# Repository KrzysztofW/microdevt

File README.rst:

Upstream Author: Krzysztof Witek

Copyright:
	 Copyright (c) 2017 Krzysztof Witek

License: GPL-2

Overview
========

Microdevt is a microcontroller development toolkit for quickly developing
embedded applications.
The toolkit provides asynchronous timers, a task scheduler and a zero-copy,
event-based TCP/IP stack. The asynchronous approach of developing Microdevt
applications allows to benefit as much as possible of the precious and very
limited resources of microcontrollers.
It is distributed freely under the GPL-2 open source license and is designed
for reliability and ease of use.

For more details see complete documentation in `docs' folder.

Supported Devices
-----------------

If you don't see a match of your microcontroller, keep in mind that it's
easy to port Microdevt code to other microcontrollers.

- Atmel AVR familly (Atmega 328P, Attiny85, Atmega2561 and many others)
- Simulavr
- X86 (for testing purposes)

TCP/IP protocols
----------------

- Ethernet
- ARP
- IP
- ICMP
- TCP (basic support with retransmissions, no window support yet)
- UDP
- DNS

Wireless Radio Frequency
------------------------

- Swen level 2 (Data Link Layer)
- Swen level 3 (Network Layer)

The Swen protocols rely on the robust RF driver (*/drivers/rf.c*) that
uses the pulse width modulated encoding to send & receive data.

The Swen L3 protocol is a unicast connection-oriented protocol and it has
been designed to be reliable and secure (uses xtea encription).
It is reliable as it notifies the user application whether or not the delivery
of data to the recipient was successful. It retransmits lost data, detects
data corruptions and uses acknowledgments.

The Swen L2 protocol can be used to send & receive unacknowledged data but also
it can record and replay generic commands from widely used 433Mhz remote
controls and gadgets.

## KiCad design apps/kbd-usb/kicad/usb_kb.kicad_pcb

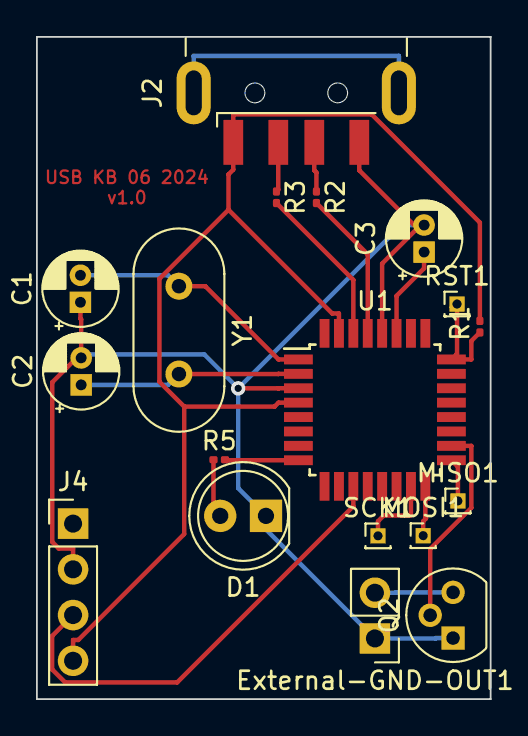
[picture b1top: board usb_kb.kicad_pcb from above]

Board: 2 copper layers, 25.2 x 36.8 mm, 18 parts (0 on the bottom side), 16 nets.

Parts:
C1, C2: C; CP_Radial_D4.0mm_P1.50mm
C3: C 1uF; CP_Radial_D4.0mm_P1.50mm
D1: LED; LED_D5.0mm
External-GND-OUT1: Conn_01x02_Male External GND SRC; PinHeader_1x02_P2.54mm_Vertical
J2: USB_A; USB_A_CNCTech_1001-011-01101_Horizontal
J4: Conn_01x04_Male SYN 480R; PinHeader_1x04_P2.54mm_Vertical
MISO1: MISO; PinHeader_1x01_P1.00mm_Vertical
MOSI1: MOSI; PinHeader_1x01_P1.00mm_Vertical
Q2: Q_NPN_BCE; TO-92
R1, R5: R10k; R_0201_0603Metric
R2, R3: R 22; R_0201_0603Metric
RST1: RST; PinHeader_1x01_P1.00mm_Vertical
SCK1: SCK; PinHeader_1x01_P1.00mm_Vertical
U1: ATmega16U2-A; TQFP-32_7x7mm_P0.8mm
Y1: Crystal; Crystal_HC49-U_Vertical

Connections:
/D+: R2.2, U1.29 (D+)
/D-: R3.2, U1.30 (D-)
/MISO_IC: MISO1.1, U1.17 (PB3)
/MOSI_IC: MOSI1.1, U1.16 (PB2)
/RST_IC: R1.2, RST1.1, U1.24 (PC1/~RESET)
/SCK_IC: SCK1.1, U1.15 (PB1)
/VCC: J2.1 (VBUS), J4.4, R1.1, U1.4 (VCC), U1.31 (UVCC)
GND: C1.1, C2.2, C3.2, D1.1 (K), External-GND-OUT1.1, J2.4 (GND), J4.2, Q2.1 (E), U1.3 (GND), U1.28 (UGND)
unnamed: C1.2, U1.1 (XTAL1), Y1.1
unnamed: C2.1, U1.2 (PC0/XTAL2), Y1.2
unnamed: D1.2 (A), R5.1
unnamed: External-GND-OUT1.2, Q2.3 (C)
unnamed: J2.2 (D-), R3.1
unnamed: J2.3 (D+), R2.1
unnamed: Q2.2 (B), U1.18 (PB4)
unnamed: R5.2, U1.8 (PD2)

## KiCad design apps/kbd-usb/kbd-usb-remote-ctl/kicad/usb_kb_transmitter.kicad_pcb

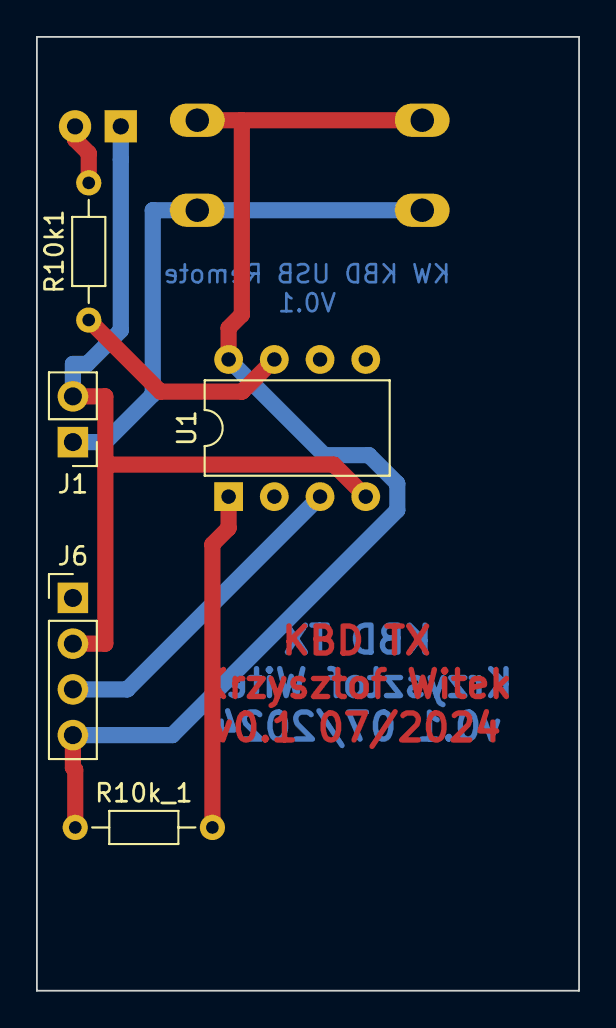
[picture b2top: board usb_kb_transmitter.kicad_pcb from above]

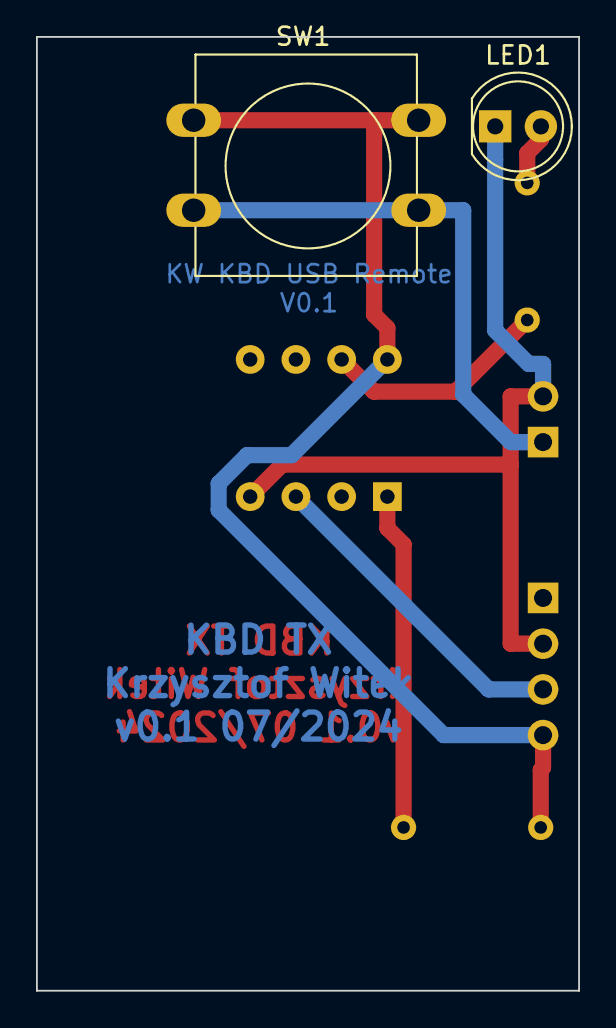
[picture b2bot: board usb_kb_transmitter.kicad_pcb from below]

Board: 2 copper layers, 30.1 x 53.0 mm, 7 parts (2 on the bottom side), 7 nets.

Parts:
J1: Conn_01x02_Female; PinHeader_1x02_P2.54mm_Vertical
J6: SYN115; PinHeader_1x04_P2.54mm_Vertical
LED1: LED; LED_D5.0mm
R10k1, R10k_1: R10k; R_Axial_DIN0204_L3.6mm_D1.6mm_P7.62mm_Horizontal
SW1: SW_MEC_5E; SW_PUSH-12mm
U1: ATtiny85-20P; DIP-8_W7.62mm

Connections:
+3.3V: J1.1, SW1.2
/T: J6.3, U1.3 (XTAL2/PB4)
/VCC: J6.4, R10k_1.1, SW1.1, U1.8 (VCC)
GND: J1.2, J6.2, LED1.1 (K), U1.4 (GND)
unnamed: LED1.2 (A), R10k1.2
unnamed: R10k1.1, U1.7 (PB2)
unnamed: R10k_1.2, U1.1 (~RESET/PB5)

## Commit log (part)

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2020-05-20 sys/list: add helpers for debugging
2020-05-20 alarm: remove dead code
2020-05-20 apps/alarm-module1: turn fan on when RH >= 80%
    Also:
    - do not compile UART code in DEBUG mode
    - allow to convert ADC input to relative humidity in %
    - always sample humidity, even when not in sleep mode
2020-05-20 apps/alarm: use a static library to save space
    This patch will allow to not include unused code in the final
    binary file. This patch breaks the simulator arch but it's fine
    as the simulator is not used in this application.
2020-05-20 arch/log: have a logging macro for debugging
2020-05-20 sys/buf: fix buf_has_room() function
2020-05-20 alarm: fix RF config
2020-05-20 net/tcp: fix tcp option parser
2020-05-20 drivers/rf: rework RF and SWEN
    - move configuration options to rf_cfg.h
    - move RF driver to 'drivers' directory
    - move 'burst' support from Swen to RF driver.
    Later on, it could be an interface parameter.
    The purpose of this rework is to have an RF driver
    that could be used with an interface object.
2020-05-20 arch/avr: take into account brown-out detector in power down mode
2020-05-20 net/socket: add BSD_COMPAT compile option
2020-05-20 net/tests: add ip and icmp tests
2020-05-20 net/swen: notify about deletion of a non-existent generic command
2020-05-20 sys/ring: fix declaring static rings outside of a structure
2020-05-20 alarm: wdt_shutdown() should not be compiled if CONFIG_TIMER_CHECKS is not set
2020-05-20 enc28j60: fix bad check on unsigned int
2020-05-20 apps/tun-driver: fix event net apps
2020-05-20 apps/alarm-module1: set the siren on duration to 1 minute
2020-05-20 net/pkt-mempool: statically allocate the pool
2020-05-20 apps/tests: change config options
    - increase the number of packets for the RF driver
    - do not test the TCP/IP stack using hash tables
2020-05-20 net: fix #ifdefs
2020-05-20 apps/alarm: use a dedicated file for GPIOs
2020-05-20 apps/alarm: fix MOD0 hw address
2020-05-20 net/udp: implement udp socket server
2020-05-20 apps/alarm-module1: disable PCINT interrupt in simulator
    This interrupt is too often active making the scheduler to
    overload.
2020-05-20 alarm: try to fix stalled enc28j60
2020-05-20 apps/alarm-module1: remove useless include
2020-05-20 apps/alarm: add sensor report command
    Replace the humidity report value by a more generic command:
    sensor report. This command will ask for the values of all
    handled sensors of a given module.
2020-05-20 mv stdio specific code to arch/*/
2020-05-20 ring: minor rework
    - dynamic ring size
    - is_empty() checks for byte size
2020-05-20 ring: make it bigger and check for errors in add_bit()
2020-05-20 net/swen-l3: notify application when peer re-connects
    Currently, when the peer re-connects without closing an existing
    association (this can happen after a reboot or a crash), the callback
    function handling the association events is not notified.
    This is not good as the application can miss important events.
    For example when the peer sends a command and reboots for whatever reason
    before the command is actually sent, the peer will never get the command
2020-05-20 net/swen-l3: fix handling reserved bytes
    Two bytes are reserved when sending a swen-l3 packet:
    one for the 'retries left' number and one for the sequence ID.
    These bytes are wrongly reserved at the end of the packet data
    because the check for the packet free space does not take into
    account the encryption with xtea which can add additional 4 bytes
    of payload.
2020-05-20 apps/alarm: remove useless comment
2020-05-20 timer: add static initializer
2020-05-20 give TX packets a higher priority over RX packets
    This will avoid packet starvation in case we receive more packets than
    we can handle.
2020-05-20 sys/buf: rename buf2staticbuf to buf2sbuf
2020-05-20 sys/list: cleanup
2020-05-20 avr/enc28j60: replace the current driver
    The current driver was too unstable. Use a different one and remove
    SPI interrupts.
2020-05-20 ring: make interrupt safe
2020-05-20 arch/avr: enable interrupts in UARTs
2020-05-20 sys/ring: have atomic operations on avr arch
    - limit the size of the ring to 256 elements on AVR in order
    to have atomic ring operations.
    - add '\0' to buf_adds
2020-05-20 Makefile: add AVR_SIMU target
2020-05-20 net/apps: do not bind tcp client sock
2020-05-20 net: add interface init/shutdown functions
2020-05-20 net/ip: make ip ttl configurable
2020-05-20 rf: rename decode_rf_cmds() to rf_decode_cmds()
2020-05-20 net/swen-l3: mark the assoc ready to read after successful association
2020-05-20 net: fix HT_STORAGE compilation
2020-05-20 build: remove include conflicts with -Isys on x86 targets
2020-05-20 sys/ring: move functions
2020-05-20 avr/usart: enable USART1
2020-05-20 rf: move configuration options to rf_cfg.h
2020-05-20 drivers/rf: allow pkt retransmission
    Use a copy of buf_t instead of the one in pkt->buf for sending
    data. This way we'll handle the race on the buffer between
    getting data from it by the driver and by the swen-l3 layer
    when retransmitting it.
2020-05-20 alarm: add watchdog reset
2020-05-20 Makefile: rework test rule
2020-05-20 sys/buf: add helpers to print bufs content
2020-05-20 fix indents
2020-05-20 apps/tun-driver: fix compilation problem on ubuntu 16.04
2020-05-20 net/swen-rc: add support for rolling codes
2020-05-20 sys/buf: make 'data' point to the current position in the buffer
2020-05-20 apps/alarm-module1: fix power management option in simulator
2020-05-20 scheduler: optimize code
    - avoid a division in calculating the number of tasks in a ring
    - fix swapped ring_irq with ring
    - run already scheduled tasks if there is no more room to schedule a new one.
    This is only done for tasks scheduled from the scheduler (not from interrupts).
2020-05-20 apps/alarm: misc fixes
2020-05-20 apps/alarm: add module configuration pointer to sensor cron function
2020-05-20 arch/avr: fix messy ADC code
2020-05-20 fix wrong printf modifier
2020-05-20 net/swen-l3: fix buggy timer reschedule
    The timer in swen_l3_task_cb() may have already been scheduled by
    he swen_l3_output() function. Make sure we don't try to reschedule
    it again.
2020-05-20 net/swen-l3: check if connected in disassociate
    Do not try to disassociate if the socket is not connected.
    Also remove the pkt pointer form debug code.
2020-05-20 net/tun-driver: add timer support
2020-05-20 net/arp: fix request tests
2020-05-20 net/pkt: remove unused packet reference counter
2020-05-20 apps/alarm-simu: fix wrong debug RF context in module1
2020-05-20 net/ip: complete input/output functions
2020-05-20 apps/alarm: add forgotten include for ISR
2020-05-20 alarm/Makefile: add reset rule and preserve eeprom flag info
2020-05-20 net/pkt: allow allocating an emergency packet
    In case there is no more packets left in the packet spool,
    we need to get rid of packets we send to free them.
    Allow to allocate a special packet from the heap that
    should be only used for sending.
2020-05-20 sys/ring: remove interrupt safe ring
    it's better to disable interrupts when using rings
    than increase their size and complexity.
2020-05-20 net/route: default route
2020-05-20 net/arp: clean up and fix type
2020-05-20 sys/buf: add helper for adding variable argument strings
2020-05-20 net/tcp-socket: misc fixes
2020-05-20 add license header
2020-05-20 docs: add documentation
    Build the documentation using doxygen, sphinx and breathe.
    TODO: Demo Apps section and module configuration.
2020-05-20 docs: add 'power management' API
2020-05-20 sys/buf: remove length from __buf_adds() function
2020-05-20 move timers, scheduler and power managment to sys folder
2020-05-20 sys/timer: abort on pending timer insertions
2020-05-20 sys/timer: add a better log for debugging
2020-05-20 drivers/ir-hx1838: add support for repeated commands
    This commit will make possible to catch burst commands,
    if the remote control button is pressed and held.
2020-05-20 sys/opts: add generic option parser
2020-05-20 net/test: fix segmentation fault
    The event's rx queue must be set.
2020-05-20 drivers/ir-hx1838: make checking inversion optional
    This will allow to easily support a much wider range of IR remotes.
2020-05-20 drivers/rf: rename the RF driver
    This driver implementation is not very used world wide. A new drivers will
    come in a subsequent patch that can encode/decode PT 2262/2272 protocol.
2020-05-20 arch/avr/timers: move definition to .h file and define __timer_subsystem_reset()
2020-05-20 docs/README: update sphinx dependencies
2020-05-20 arch/timer: add helper to stop timer subsystem
    This patch allows to stop the architecture dependant timer
    interrupt if no timers are registered reducing the overall
    power consumption.
2020-05-20 drivers/ir: add optional 8-bit address checking
2020-05-20 net/swen: add a helper to get human readable generic cmd status
2020-05-20 sys/opts: size optimizations
    Also add signed arg types.
2020-05-20 net/swen: optimize L2 header
    Warning, this commit breaks the backward compatibility.
    There is no need to add the 'protocol' byte in the swen L2 layer
    if no upper layer are supported.
    Also, the checksum field should be place at an odd position (byte boundaries)
    in order to avoid an htons() call.
2020-05-20 common.mk: add syntax-checking rule for emacs flymake mode
2020-05-20 net/swen: disable 'sending to us' feature
2020-05-20 docs: fix compilation
    - fix power management .h file include
    - add dependencies in the doc readme file
    - override master_doc variable in conf.py
2020-05-20 drivers/ir-hx1838: be more tolerant in error detection
2020-05-20 Makefile: move common stuff to a generic file
2020-05-20 net/swen: replay recorded generic commands
2020-05-20 sys/buf: add buf_parse_long() helper
    This helper will allow to parse a long integer in a buffer.
2020-05-20 pkt-mempool: fix emergency packet reset
2020-05-20 net/swen: erase generic command storage at initialization
2020-05-22 docs: add home page link
2020-06-21 alarm: increase fan activity
2020-07-21 arch/avr: add 8-bit ADC read function
2020-07-21 apps/water_pump: configurable & automatic water pumping app
    This simple app will start a water pump every 24h for 10 seconds
    to water plants. The power of the pump is controled by an adjustable
    resistor that triggers a PWM.
2020-07-22 arch/avr: use correct define for WDTCSR register
2020-08-12 apps/watering-pump: fix reset loop by watchdog
2020-09-09 docs: fix phrasing
2021-06-22 apps/alarm: add missing MIN_HUMIDITY_VALUE definition
2021-06-28 sys/list: fix coding rules
2021-06-28 net/tcp: fix tcp_conn leak at shutdown
2021-07-08 apps/alarm: don't compile disabled features
2021-07-08 apps/water-pump: add GPIO helpers
2021-11-10 apps/timer-switch: add new application
    This application listens for an event on an interrupt then sets a timer
    (using a watchdog to save power) for 5 hours before turning the output off.
2023-03-25 sys/buf: add len check in buf_skip()
2024-06-21 apps/watering-pump: set idle time to 24 hours
2024-07-10 apps/kbd-usb: cleanup makefile
2024-07-24 apps/kbd-usb: add RF receiver
2025-05-01 apps/mosquito-trap: add mosquito trap app
2025-05-01 apps/kbd-usb: add script compiler
2025-05-01 apps/kbd-usb/kbd-usb-remote-ctl: update kicad projet
2025-05-03 apps/kbd-usb: do not load EEPROM data to RAM
    Use EEPROM storage directly instead of loading it to RAM.
    This allows to use more EEPROM storage without over loading
    the RAM space.
2025-05-07 apps/kbd-usb: add RF remote control
    This commit introduces the option to disable USB and KBD (USB keyboard) features
    in order to ease debugging.
    The code is taken (and heavily simplified) from drivers/rf.c as it is too large
    to be used directly.
2025-05-12 apps/kbd-usb: fix keyboard layout modifiers
2025-05-12 apps/kbd-usb: implement special meta keys
2025-05-16 apps/kbd-usb: do not erase the EEPROM after flashing
